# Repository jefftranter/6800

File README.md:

# 6800
Code related to the Motorola 6800 microprocessor.

Files written by me are released under the following license:

Copyright (C) by Jeff Tranter <tranter@pobox.com>

Licensed under the Apache License, Version 2.0 (the "License");
you may not use this file except in compliance with the License.
You may obtain a copy of the License at

  http://www.apache.org/licenses/LICENSE-2.0

Unless required by applicable law or agreed to in writing, software
distributed under the License is distributed on an "AS IS" BASIS,
WITHOUT WARRANTIES OR CONDITIONS OF ANY KIND, either express or implied.
See the License for the specific language governing permissions and
limitations under the License.

Documentation written by me is licensed under a Creative Commons
Attribution 4.0 International License.
See https://creativecommons.org/licenses/by/4.0/

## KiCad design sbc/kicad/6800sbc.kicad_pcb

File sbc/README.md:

6800 Single Board Computer

This is a 6800-based single board computer design. It has the
following features:

* 6802 CPU running at 1.0 MHz
* 32K of RAM
* 16K of EPROM
* Hex keypad and 7-segment LED display interface
* Parallel interface using 6821 PIA (2 8-bit parallel ports)
* Serial interface using 6850 UART with TTL levels for FTDI USB serial adaptor
* Various power options: regulated 5VDC in (e.g. via USB), unregulated 8-25 VDC in, unregulated 8-25 AC in, or 120/220 VAC in via external AC adaptor or transformer (i.e. wall-wart)
* Address decoding using CPLD (Can adjust memory map by reprogramming CPLD)
* 50/60 Hz interrupt support if powered by AC input
* Expansion connector with all CPU bus signals
* Open Source hardware design, including PCB layout, using Kicad

The design is roughly based on the Heathkit ET-6800 CPU trainer with
additional features, some taken from the Heathkit ETA-3400 expander.
It can run a modified version of the ET-6800/ET-3400 firmware and
other firmware including a serial monitor and BASIC.

MEMORY MAP

```
+----------+-----------+----------+
| Function | Addresses | Comments |
+----------+-----------+----------+
| ROM      | C000-FFFF |   16K    |
+----------+-----------+----------+
| 6850 ACIA| 8300-8301 |          |
+----------+-----------+----------+
| 6821 PIA | 8200-8203 |          |
+----------+-----------+----------+
| Display  | 8110-816F |          |
+----------+-----------+----------+
| Keyboard | 8003-800E |          |
+----------+-----------+----------+
| RAM      | 0000-7FFF |   32K    |
+----------+-----------+----------+
```

JUMPERS AND CONNECTORS

```
J1 AC/DC IN Connector to power board from unregulated AC or DC input.
J2 5V IN Connector to power board from regulated 5 Volt input.
J3 EXPANSION Connector for expansion connector to CPU bus signals.
J4 LTC Jumper to select if AC input generates IRQ or NMI interrupts.
J5 PARALLEL PORT Connector for 2 8-bit parallel i/o ports from PIA.
J6 TX DATA SELECT Jumper to select whether to use ACIA or PIA for serial output.
J7 RX DATA SELECT Jumper to select whether to use ACIA or PIA for serial input.
J8 USB POWER Jumper to select powering board from USB FTDI connector.
J9 FTDI SERIAL Connector to a 6 pin FTDI USB serial adaptor for console.
J11 SEGMENT TEST Jumper to light all LED segments for testing.
J12 REG. POWER Jumper to select powering board from unregulated AC/DC input.
J10 PA1 Jumper to select baud rate for PIA serial interface.
J13 PA2 Jumper to select baud rate for PIA serial interface.
J14 PA3 Jumper to select baud rate for PIA serial interface.
J15 PA4 Jumper to select baud rate for PIA serial interface.
J16 PA5 Jumper to select baud rate for PIA serial interface.
J17 PA6 Jumper to select baud rate for PIA serial interface.

Serial Select Jumpers:
ACIA: J6 1-2, J7 2-3
PIA:  J6 2-3, J7 1-2

Baud Rate Jumpers:
+---+---+---+---+---+---+----+
|PA1|PA2|PA3|PA4|PA5|PA6|RATE|
+---+---+---+---+---+---+----+
| H | H | H | - | - | - | 110|
| L | L | L | - | - | - | 300|
| H | L | H | - | - | - | 600|
| L | L | H | - | - | - |1200|
| H | H | L | - | - | - |2400|
| L | H | L | - | - | - |4800|
| H | L | L | - | - | - |9600|
+---+---+---+---+---+---+----+
```

ASSEMBLY NOTES

Assembly using a PCB with the provided Gerber files is straightforward
and uses all though-hole components. It is recommended to start with
lowest height components (e.g. resistors). All ICs should be mounted
on sockets. A machined socket is recommended for the EPROM so it can
be more easily replaced when reprogrammed.

You will need a way to program the EPROM and CPLD chips.

If problems are encountered, these are the most common issues to check
for:

- Check for solder opens or shorts
- Check for bent pins under IC sockets
- Check that all parts are correct values and installed with correct orientation
- Make sure PROM and CPLD are correctly programmed
- Check for 5V power, CPU clock
- Check for ACIA clock

To test memory, you can run the memory test at address EA34. It should
display the top memory address (7FFF) and increment the test cycle
count without stopping.

To test the serial output from the PIA, set jumpers for PIA output and
desired baud rate, and run the routine at EAF6. It should continuously
output "THIS IS A TERMINAL TEST".

POWER REQUIREMENTS

Typical current requirement if powered by USB is 560 mA. A 1 amp USB
power source is recommended (note that some USB power supplies and
older USB ports can only supply 0.5A).

It can be powered from unregulated AC or DC input. It can operate from
8 to 25 volts DC either polarity. Make sure the maximum voltage
rating of C2 is not exceeded. For AC input, change the value of C2 to
2000 uF or more. AC input is required if you want to use the AC line
(50/60 Hz) interrupt feature.

Current consumption for unregulated input should be between 400 and
600mA. If the 7805 regulator gets hot you might want to mount a
heatsink on it.

OTHER NOTES

If you want to use port A of the PIA for i/o, be sure to remove any
jumpers at J6, J7, and J10-J17.

The Heathkit ETA-3400 had support for a cassette tape interface. This
is not present, so any monitor or Basic commands related to cassette
will not function.

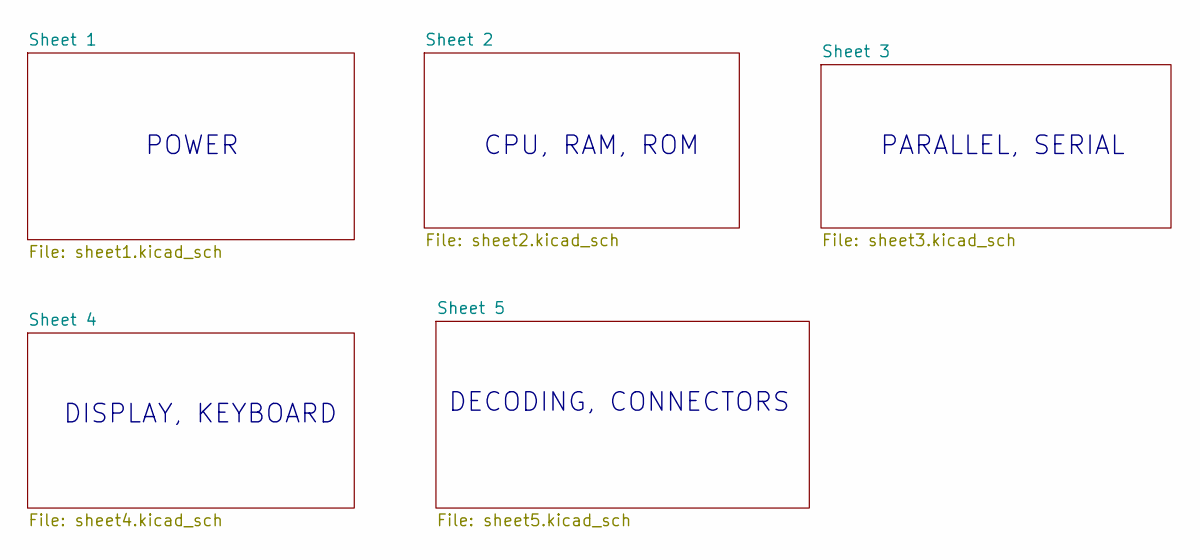
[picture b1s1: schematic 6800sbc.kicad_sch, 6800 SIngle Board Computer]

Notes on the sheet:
DECODING, CONNECTORS
PARALLEL, SERIAL
CPU, RAM, ROM
DISPLAY, KEYBOARD
POWER

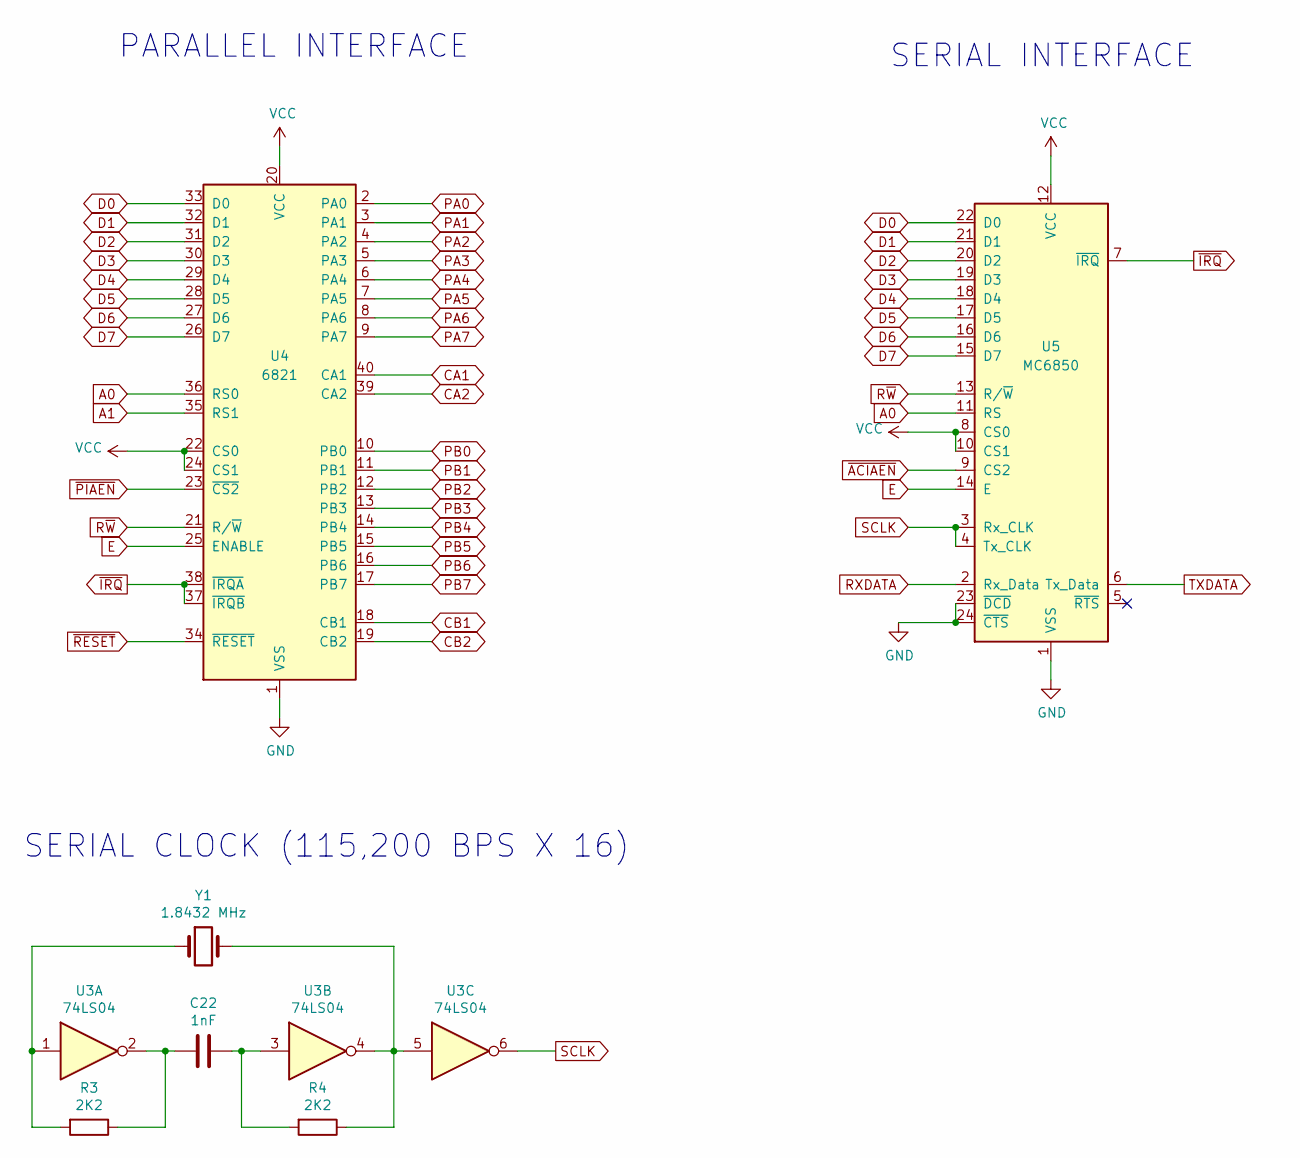
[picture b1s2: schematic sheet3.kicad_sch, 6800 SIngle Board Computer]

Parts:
C22: 1nF; C_Disc_D5.0mm_W2.5mm_P5.00mm
R3, R4: 2K2; R_Axial_DIN0204_L3.6mm_D1.6mm_P7.62mm_Horizontal
U3: 74LS04; DIP-14_W7.62mm_Socket
U4: 6821; DIP-40_W15.24mm
U5: MC6850; DIP-24_W15.24mm
Y1: 1.8432 MHz; Crystal_HC18-U_Vertical

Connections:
A0: U4.36 (RS0), U5.11 (RS); also elsewhere on the board
A1: U4.35 (RS1); also elsewhere on the board
CA1: U4.40 (CA1); also elsewhere on the board
CA2: U4.39 (CA2); also elsewhere on the board
CB1: U4.18 (CB1); also elsewhere on the board
CB2: U4.19 (CB2); also elsewhere on the board
D0: U4.33 (D0), U5.22 (D0); also elsewhere on the board
D1: U4.32 (D1), U5.21 (D1); also elsewhere on the board
D2: U4.31 (D2), U5.20 (D2); also elsewhere on the board
D3: U4.30 (D3), U5.19 (D3); also elsewhere on the board
D4: U4.29 (D4), U5.18 (D4); also elsewhere on the board
D5: U4.28 (D5), U5.17 (D5); also elsewhere on the board
D6: U4.27 (D6), U5.16 (D6); also elsewhere on the board
D7: U4.26 (D7), U5.15 (D7); also elsewhere on the board
GND: U4.1 (VSS), U5.1 (VSS), U5.23 (~DCD), U5.24 (~CTS); also elsewhere on the board
unnamed: C22.1, R4.2, U3.3
unnamed: R4.1, U3.4, U3.5, Y1.2
unnamed 154: U3.10; also elsewhere on the board
PA0: U4.2 (PA0); also elsewhere on the board
PA1: U4.3 (PA1); also elsewhere on the board
PA2: U4.4 (PA2); also elsewhere on the board
PA3: U4.5 (PA3); also elsewhere on the board
PA4: U4.6 (PA4); also elsewhere on the board
PA5: U4.7 (PA5); also elsewhere on the board
PA6: U4.8 (PA6); also elsewhere on the board
PA7: U4.9 (PA7); also elsewhere on the board
PB0: U4.10 (PB0); also elsewhere on the board
PB1: U4.11 (PB1); also elsewhere on the board
PB2: U4.12 (PB2); also elsewhere on the board
PB3: U4.13 (PB3); also elsewhere on the board
PB4: U4.14 (PB4); also elsewhere on the board
PB5: U4.15 (PB5); also elsewhere on the board
PB6: U4.16 (PB6); also elsewhere on the board
PB7: U4.17 (PB7); also elsewhere on the board
RXDATA: U5.2 (Rx_Data); also elsewhere on the board
SCLK: U3.6, U5.3 (Rx_CLK), U5.4 (Tx_CLK); also elsewhere on the board
TXDATA: U5.6 (Tx_Data); also elsewhere on the board
VCC: U4.20 (VCC), U4.22 (CS0), U4.24 (CS1), U5.8 (CS0), U5.10 (CS1), U5.12 (VCC); also elsewhere on the board
~ACIAEN: U5.9 (CS2); also elsewhere on the board
~IRQ: U4.37 (~IRQB), U4.38 (~IRQA), U5.7 (~IRQ); also elsewhere on the board
~PIAEN: U4.23 (~CS2); also elsewhere on the board
~RESET: U4.34 (~RESET); also elsewhere on the board

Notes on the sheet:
PARALLEL INTERFACE
SERIAL CLOCK (115,200 BPS X 16)
SERIAL INTERFACE

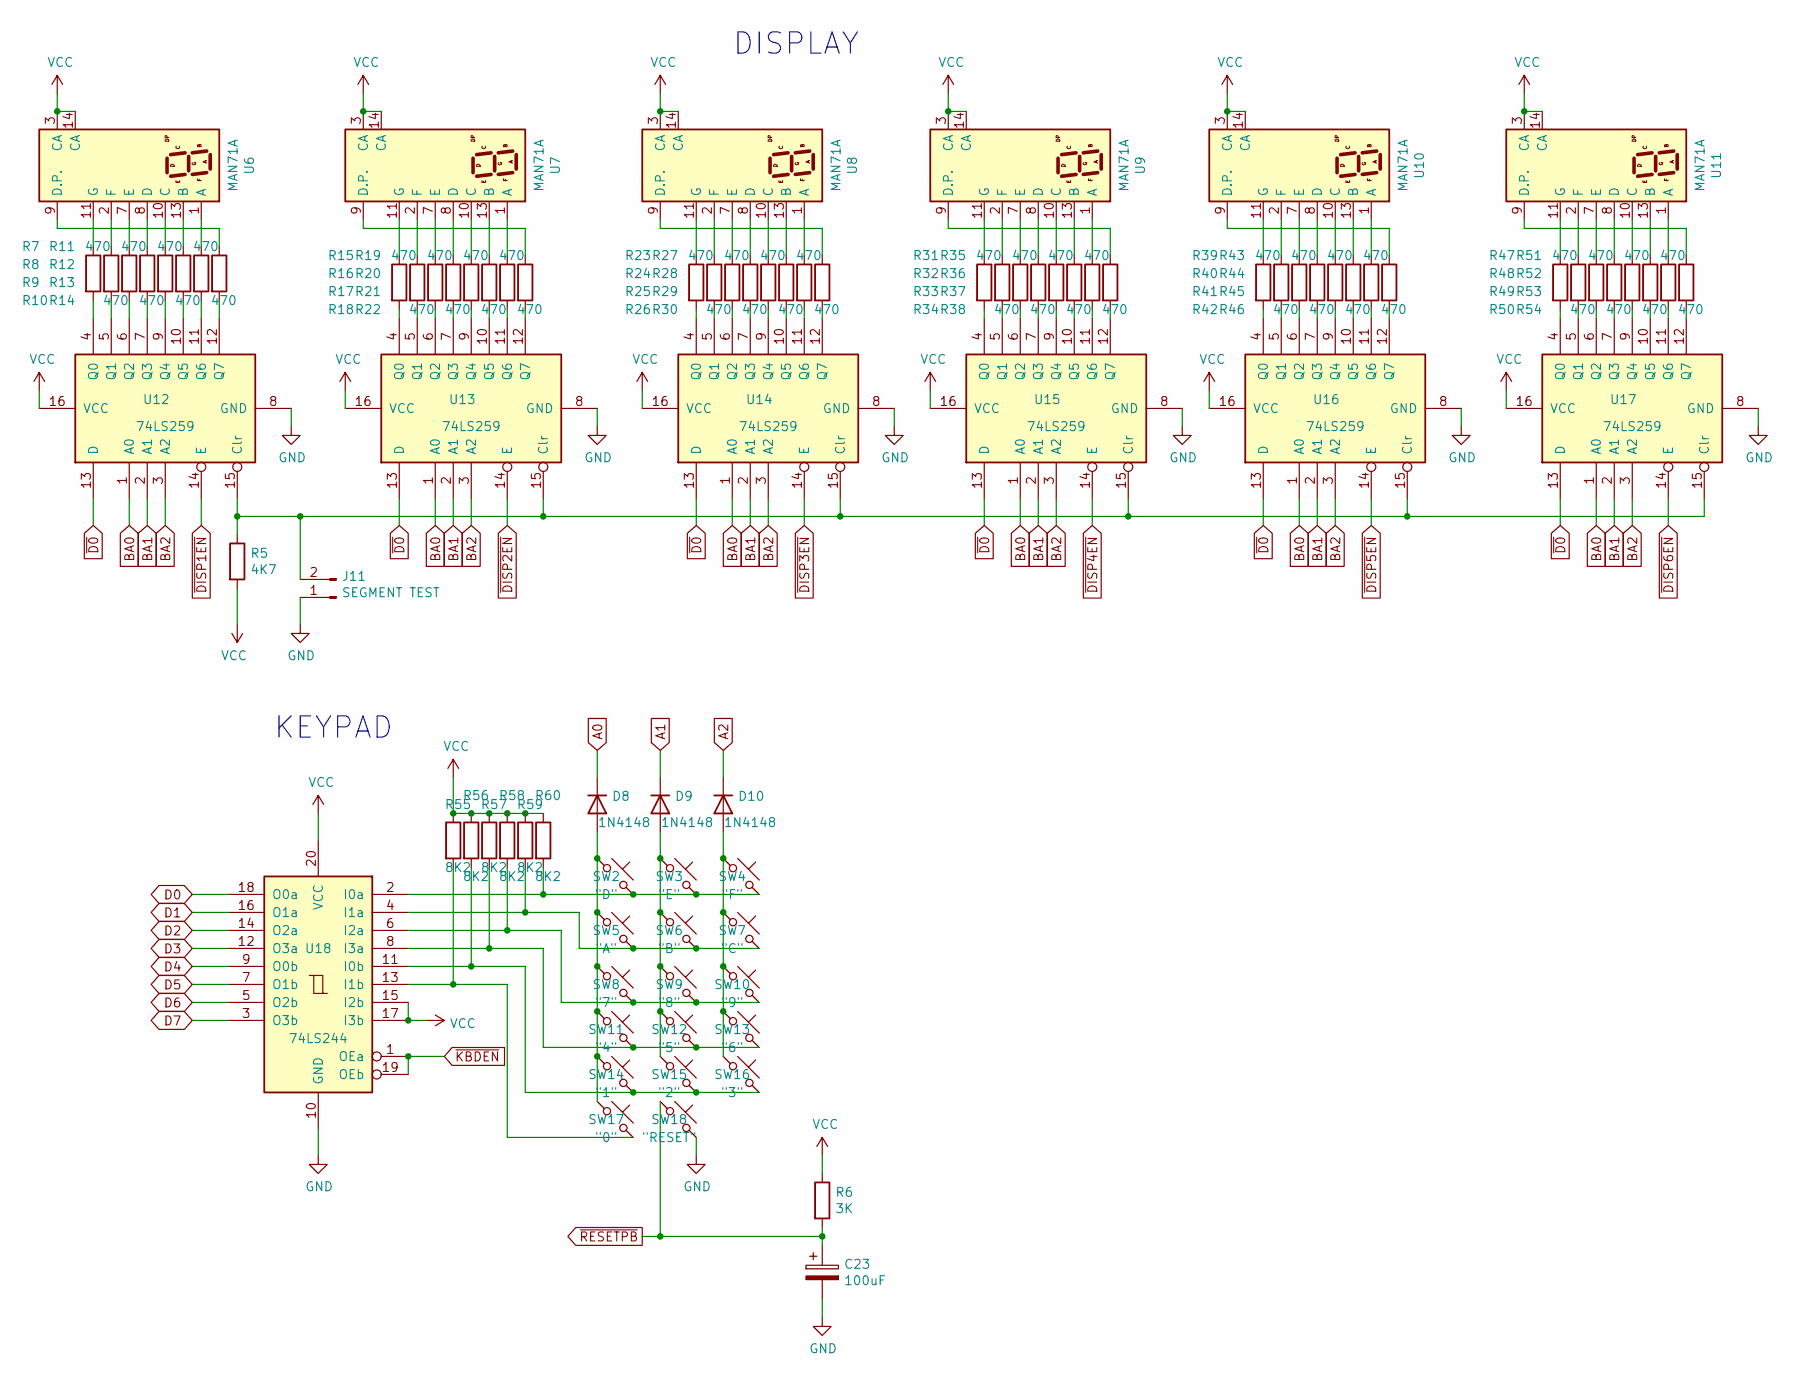
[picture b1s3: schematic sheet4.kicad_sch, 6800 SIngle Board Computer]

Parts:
C23: 100uF; CP_Radial_D4.0mm_P2.00mm
D8, D9, D10: 1N4148; D_DO-35_SOD27_P7.62mm_Horizontal
J11: SEGMENT TEST; PinHeader_1x02_P2.54mm_Vertical
R5: 4K7; R_Axial_DIN0204_L3.6mm_D1.6mm_P7.62mm_Horizontal
R6: 3K; R_Axial_DIN0204_L3.6mm_D1.6mm_P7.62mm_Horizontal
R7, R8, R9, R10, R11, R12, R13, R14, R15, R16, R17, R18, R19, R20, R21, R22, R23, R24, R25, R26, R27, R28, R29, R30, R31, R32, R33, R34, R35, R36, R37, R38, R39, R40, R41, R42, R43, R44, R45, R46, R47, R48, R49, R50, R51, R52, R53, R54: 470; R_Axial_DIN0204_L3.6mm_D1.6mm_P7.62mm_Horizontal
R55, R56, R57, R58, R59, R60: 8K2; R_Axial_DIN0204_L3.6mm_D1.6mm_P7.62mm_Horizontal
SW2: "D"; SW_PUSH_6mm_H4.3mm
SW3: "E"; SW_PUSH_6mm_H4.3mm
SW4: "F"; SW_PUSH_6mm_H4.3mm
SW5: "A"; SW_PUSH_6mm_H4.3mm
SW6: "B"; SW_PUSH_6mm_H4.3mm
SW7: "C"; SW_PUSH_6mm_H4.3mm
SW8: "7"; SW_PUSH_6mm_H4.3mm
SW9: "8"; SW_PUSH_6mm_H4.3mm
SW10: "9"; SW_PUSH_6mm_H4.3mm
SW11: "4"; SW_PUSH_6mm_H4.3mm
SW12: "5"; SW_PUSH_6mm_H4.3mm
SW13: "6"; SW_PUSH_6mm_H4.3mm
SW14: "1"; SW_PUSH_6mm_H4.3mm
SW15: "2"; SW_PUSH_6mm_H4.3mm
SW16: "3"; SW_PUSH_6mm_H4.3mm
SW17: "0"; SW_PUSH_6mm_H4.3mm
SW18: "RESET"; SW_PUSH_6mm_H4.3mm
U6, U7, U8, U9, U10, U11: MAN71A
U12, U13, U14, U15, U16, U17: 74LS259; DIP-16_W7.62mm_Socket
U18: 74LS244; DIP-20_W7.62mm_Socket

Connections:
A0: D8.1 (K); also elsewhere on the board
A1: D9.1 (K); also elsewhere on the board
A2: D10.1 (K); also elsewhere on the board
BA0: U12.1 (A0), U13.1 (A0), U14.1 (A0), U15.1 (A0), U16.1 (A0), U17.1 (A0); also elsewhere on the board
BA1: U12.2 (A1), U13.2 (A1), U14.2 (A1), U15.2 (A1), U16.2 (A1), U17.2 (A1); also elsewhere on the board
BA2: U12.3 (A2), U13.3 (A2), U14.3 (A2), U15.3 (A2), U16.3 (A2), U17.3 (A2); also elsewhere on the board
D0: U18.18 (O0a); also elsewhere on the board
D1: U18.16 (O1a); also elsewhere on the board
D2: U18.14 (O2a); also elsewhere on the board
D3: U18.12 (O3a); also elsewhere on the board
D4: U18.9 (O0b); also elsewhere on the board
D5: U18.7 (O1b); also elsewhere on the board
D6: U18.5 (O2b); also elsewhere on the board
D7: U18.3 (O3b); also elsewhere on the board
GND: C23.2, J11.1, SW18.2, U12.8 (GND), U13.8 (GND), U14.8 (GND), U15.8 (GND), U16.8 (GND), U17.8 (GND), U18.10 (GND); also elsewhere on the board
unnamed: D8.2 (A), SW2.1, SW5.1, SW8.1, SW11.1, SW14.1, SW17.1
unnamed: D9.2 (A), SW3.1, SW6.1, SW9.1, SW12.1, SW15.1
unnamed: D10.2 (A), SW4.1, SW7.1, SW10.1, SW13.1, SW16.1
unnamed: J11.2, R5.1, U12.15 (Clr), U13.15 (Clr), U14.15 (Clr), U15.15 (Clr), U16.15 (Clr), U17.15 (Clr)
unnamed: R7.1, U6.11 (G)
unnamed: R7.2, U12.4 (Q0)
unnamed: R8.1, U6.2 (F)
unnamed: R8.2, U12.5 (Q1)
unnamed: R9.1, U6.7 (E)
unnamed: R9.2, U12.6 (Q2)
unnamed: R10.1, U6.8 (D)
unnamed: R10.2, U12.7 (Q3)
unnamed: R11.1, U6.10 (C)
unnamed: R11.2, U12.9 (Q4)
unnamed: R12.1, U6.13 (B)
unnamed: R12.2, U12.10 (Q5)
unnamed: R13.1, U6.1 (A)
unnamed: R13.2, U12.11 (Q6)
unnamed: R14.1, U6.9 (D.P.)
unnamed: R14.2, U12.12 (Q7)
unnamed: R15.1, U7.11 (G)
unnamed: R15.2, U13.4 (Q0)
unnamed: R16.1, U7.2 (F)
unnamed: R16.2, U13.5 (Q1)
unnamed: R17.1, U7.7 (E)
unnamed: R17.2, U13.6 (Q2)
unnamed: R18.1, U7.8 (D)
unnamed: R18.2, U13.7 (Q3)
unnamed: R19.1, U7.10 (C)
unnamed: R19.2, U13.9 (Q4)
unnamed: R20.1, U7.13 (B)
unnamed: R20.2, U13.10 (Q5)
unnamed: R21.1, U7.1 (A)
unnamed: R21.2, U13.11 (Q6)
unnamed: R22.1, U7.9 (D.P.)
unnamed: R22.2, U13.12 (Q7)
unnamed: R23.1, U8.11 (G)
unnamed: R23.2, U14.4 (Q0)
unnamed: R24.1, U8.2 (F)
unnamed: R24.2, U14.5 (Q1)
unnamed: R25.1, U8.7 (E)
unnamed: R25.2, U14.6 (Q2)
unnamed: R26.1, U8.8 (D)
unnamed: R26.2, U14.7 (Q3)
unnamed: R27.1, U8.10 (C)
unnamed: R27.2, U14.9 (Q4)
unnamed: R28.1, U8.13 (B)
unnamed: R28.2, U14.10 (Q5)
unnamed: R29.1, U8.1 (A)
unnamed: R29.2, U14.11 (Q6)
unnamed: R30.1, U8.9 (D.P.)
unnamed: R30.2, U14.12 (Q7)
unnamed: R31.1, U9.11 (G)
unnamed: R31.2, U15.4 (Q0)
unnamed: R32.1, U9.2 (F)
unnamed: R32.2, U15.5 (Q1)
unnamed: R33.1, U9.7 (E)
unnamed: R33.2, U15.6 (Q2)
unnamed: R34.1, U9.8 (D)
unnamed: R34.2, U15.7 (Q3)
unnamed: R35.1, U9.10 (C)
unnamed: R35.2, U15.9 (Q4)
unnamed: R36.1, U9.13 (B)
unnamed: R36.2, U15.10 (Q5)
unnamed: R37.1, U9.1 (A)
unnamed: R37.2, U15.11 (Q6)
unnamed: R38.1, U9.9 (D.P.)
unnamed: R38.2, U15.12 (Q7)
unnamed: R39.1, U10.11 (G)
unnamed: R39.2, U16.4 (Q0)
unnamed: R40.1, U10.2 (F)
unnamed: R40.2, U16.5 (Q1)
unnamed: R41.1, U10.7 (E)
unnamed: R41.2, U16.6 (Q2)
unnamed: R42.1, U10.8 (D)
unnamed: R42.2, U16.7 (Q3)
unnamed: R43.1, U10.10 (C)
unnamed: R43.2, U16.9 (Q4)
unnamed: R44.1, U10.13 (B)
unnamed: R44.2, U16.10 (Q5)
unnamed: R45.1, U10.1 (A)
unnamed: R45.2, U16.11 (Q6)
unnamed: R46.1, U10.9 (D.P.)
unnamed: R46.2, U16.12 (Q7)
unnamed: R47.1, U11.11 (G)
unnamed: R47.2, U17.4 (Q0)
unnamed: R48.1, U11.2 (F)
unnamed: R48.2, U17.5 (Q1)
unnamed: R49.1, U11.7 (E)
unnamed: R49.2, U17.6 (Q2)
unnamed: R50.1, U11.8 (D)
unnamed: R50.2, U17.7 (Q3)
unnamed: R51.1, U11.10 (C)
unnamed: R51.2, U17.9 (Q4)
unnamed: R52.1, U11.13 (B)
unnamed: R52.2, U17.10 (Q5)
unnamed: R53.1, U11.1 (A)
unnamed: R53.2, U17.11 (Q6)
unnamed: R54.1, U11.9 (D.P.)
unnamed: R54.2, U17.12 (Q7)
unnamed: R55.2, SW17.2, U18.13 (I1b)
unnamed: R56.2, SW14.2, SW15.2, SW16.2, U18.11 (I0b)
unnamed: R57.2, SW11.2, SW12.2, SW13.2, U18.8 (I3a)
unnamed: R58.2, SW8.2, SW9.2, SW10.2, U18.6 (I2a)
unnamed: R59.2, SW5.2, SW6.2, SW7.2, U18.4 (I1a)
unnamed: R60.2, SW2.2, SW3.2, SW4.2, U18.2 (I0a)
VCC: R5.2, R6.1, R55.1, R56.1, R57.1, R58.1, R59.1, R60.1, U6.3 (CA), U6.14 (CA), U7.3 (CA), U7.14 (CA), U8.3 (CA), U8.14 (CA), U9.3 (CA), U9.14 (CA), U10.3 (CA), U10.14 (CA), U11.3 (CA), U11.14 (CA), U12.16 (VCC), U13.16 (VCC), U14.16 (VCC), U15.16 (VCC), U16.16 (VCC), U17.16 (VCC), U18.15 (I2b), U18.17 (I3b), U18.20 (VCC); also elsewhere on the board
~D0: U12.13 (D), U13.13 (D), U14.13 (D), U15.13 (D), U16.13 (D), U17.13 (D); also elsewhere on the board
~DISP1EN: U12.14 (E); also elsewhere on the board
~DISP2EN: U13.14 (E); also elsewhere on the board
~DISP3EN: U14.14 (E); also elsewhere on the board
~DISP4EN: U15.14 (E); also elsewhere on the board
~DISP5EN: U16.14 (E); also elsewhere on the board
~DISP6EN: U17.14 (E); also elsewhere on the board
~KBDEN: U18.1 (OEa), U18.19 (OEb); also elsewhere on the board
~RESETPB: C23.1, R6.2, SW18.1; also elsewhere on the board

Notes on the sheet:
DISPLAY
KEYPAD

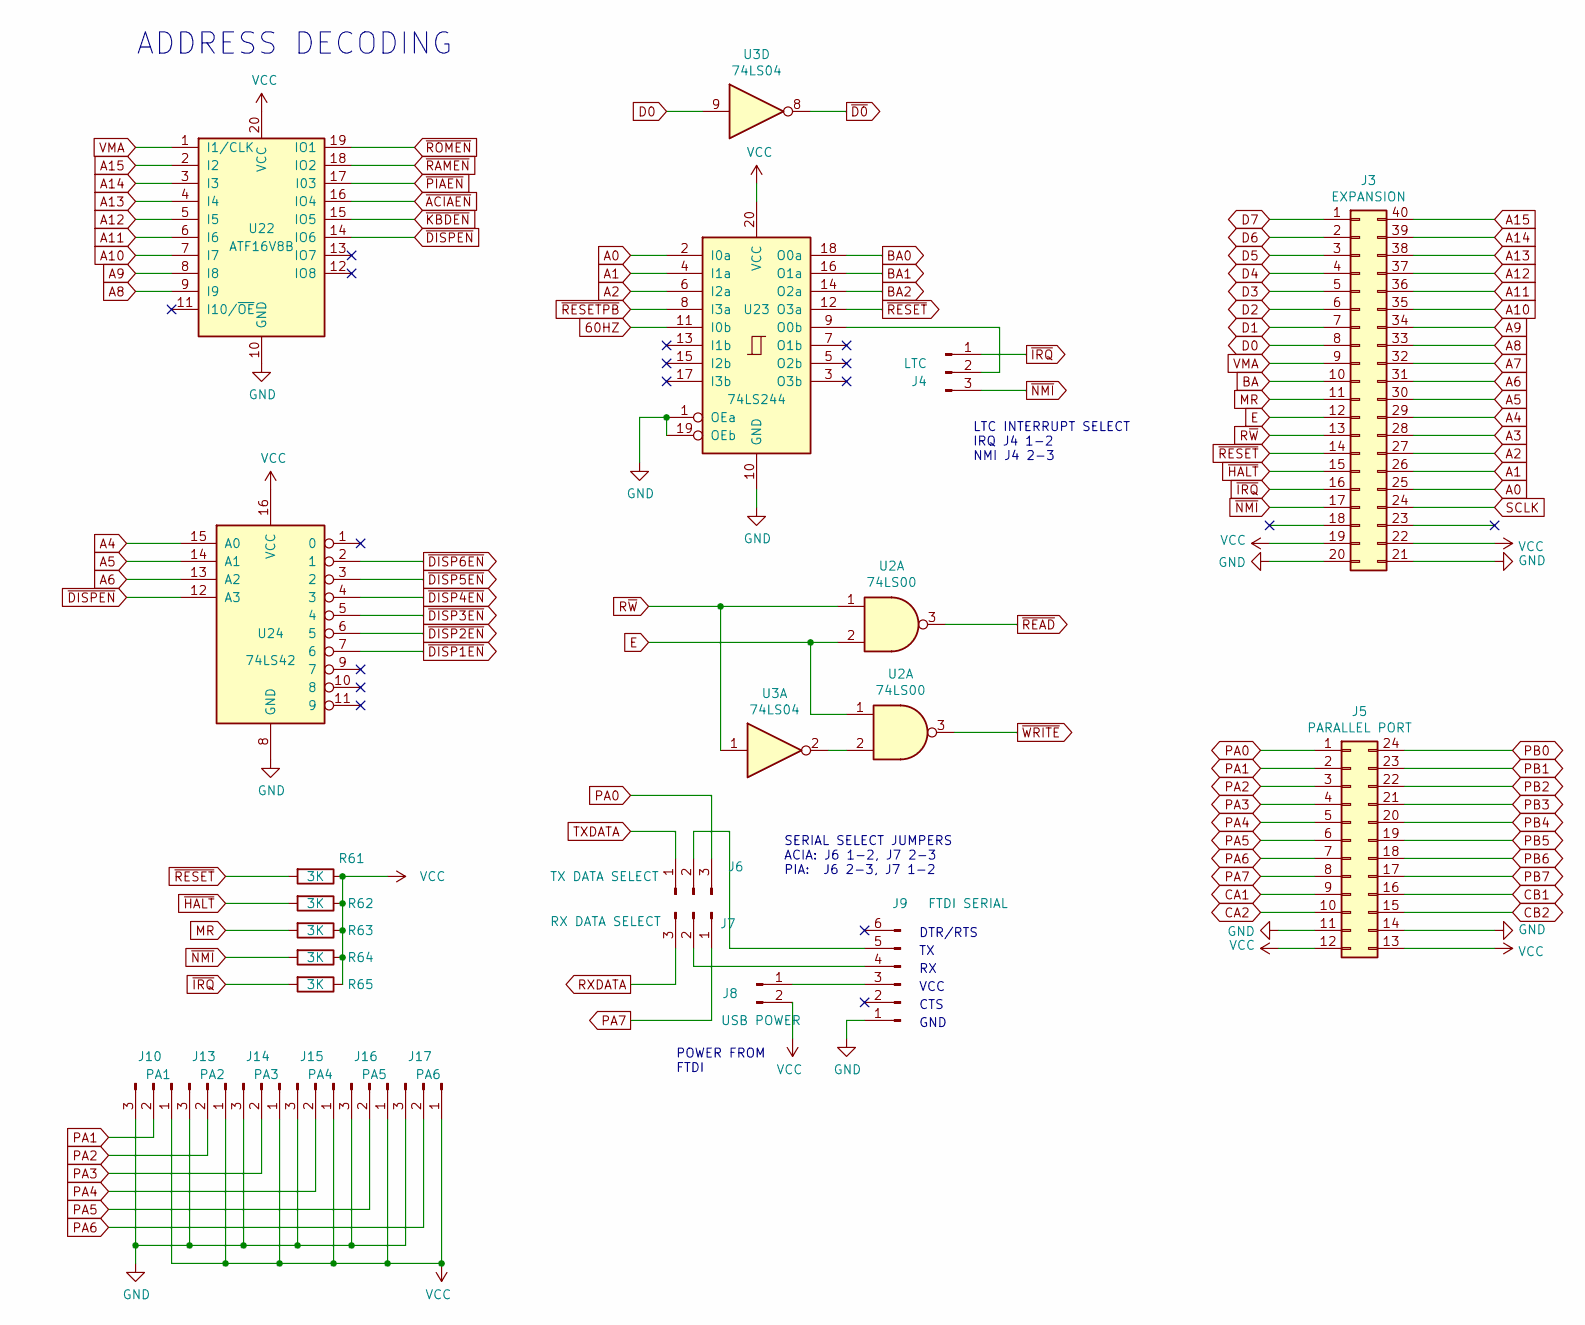
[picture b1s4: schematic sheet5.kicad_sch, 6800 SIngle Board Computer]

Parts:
J3: EXPANSION; PinHeader_2x20_P2.54mm_Vertical
J4: LTC; PinHeader_1x03_P2.54mm_Vertical
J5: PARALLEL PORT; PinHeader_2x12_P2.54mm_Vertical
J6: TX DATA SELECT; PinHeader_1x03_P2.54mm_Vertical
J7: RX DATA SELECT; PinHeader_1x03_P2.54mm_Vertical
J8: USB POWER; PinHeader_1x02_P2.54mm_Vertical
J9: FTDI SERIAL; PinHeader_1x06_P2.54mm_Vertical
J10: PA1; PinHeader_1x03_P2.54mm_Vertical
J13: PA2; PinHeader_1x03_P2.54mm_Vertical
J14: PA3; PinHeader_1x03_P2.54mm_Vertical
J15: PA4; PinHeader_1x03_P2.54mm_Vertical
J16: PA5; PinHeader_1x03_P2.54mm_Vertical
J17: PA6; PinHeader_1x03_P2.54mm_Vertical
R61, R62, R63, R64, R65: 3K; R_Axial_DIN0204_L3.6mm_D1.6mm_P7.62mm_Horizontal
U2: 74LS00; DIP-14_W7.62mm_Socket
U3: 74LS04; DIP-14_W7.62mm_Socket
U22: ATF16V8B; DIP-20_W7.62mm_Socket
U23: 74LS244; DIP-20_W7.62mm_Socket
U24: 74LS42; DIP-16_W7.62mm_Socket

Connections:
60HZ: U23.11 (I0b); also elsewhere on the board
A0: J3.25, U23.2 (I0a); also elsewhere on the board
A1: J3.26, U23.4 (I1a); also elsewhere on the board
A2: J3.27, U23.6 (I2a); also elsewhere on the board
A3: J3.28; also elsewhere on the board
A4: J3.29, U24.15 (A0); also elsewhere on the board
A5: J3.30, U24.14 (A1); also elsewhere on the board
A6: J3.31, U24.13 (A2); also elsewhere on the board
A7: J3.32; also elsewhere on the board
A8: J3.33, U22.9 (I9); also elsewhere on the board
A9: J3.34, U22.8 (I8); also elsewhere on the board
A10: J3.35, U22.7 (I7); also elsewhere on the board
A11: J3.36, U22.6 (I6); also elsewhere on the board
A12: J3.37, U22.5 (I5); also elsewhere on the board
A13: J3.38, U22.4 (I4); also elsewhere on the board
A14: J3.39, U22.3 (I3); also elsewhere on the board
A15: J3.40, U22.2 (I2); also elsewhere on the board
BA: J3.10; also elsewhere on the board
BA0: U23.18 (O0a); also elsewhere on the board
BA1: U23.16 (O1a); also elsewhere on the board
BA2: U23.14 (O2a); also elsewhere on the board
CA1: J5.9; also elsewhere on the board
CA2: J5.10; also elsewhere on the board
CB1: J5.16; also elsewhere on the board
CB2: J5.15; also elsewhere on the board
D0: J3.8, U3.9; also elsewhere on the board
D1: J3.7; also elsewhere on the board
D2: J3.6; also elsewhere on the board
D3: J3.5; also elsewhere on the board
D4: J3.4; also elsewhere on the board
D5: J3.3; also elsewhere on the board
D6: J3.2; also elsewhere on the board
D7: J3.1; also elsewhere on the board
GND: J3.20, J3.21, J5.11, J5.14, J9.1, J10.3, J13.3, J14.3, J15.3, J16.3, J17.3, U22.10 (GND), U23.1 (OEa), U23.10 (GND), U23.19 (OEb), U24.8 (GND); also elsewhere on the board
MR: J3.11, R63.2; also elsewhere on the board
unnamed: J4.2, U23.9 (O0b)
unnamed: J6.2, J9.5
unnamed: J7.2, J9.4
unnamed: J8.1, J9.3
unnamed: U2.5, U3.10
PA0: J5.1, J6.3; also elsewhere on the board
PA1: J5.2, J10.2; also elsewhere on the board
PA2: J5.3, J13.2; also elsewhere on the board
PA3: J5.4, J14.2; also elsewhere on the board
PA4: J5.5, J15.2; also elsewhere on the board
PA5: J5.6, J16.2; also elsewhere on the board
PA6: J5.7, J17.2; also elsewhere on the board
PA7: J5.8, J7.1; also elsewhere on the board
PB0: J5.24; also elsewhere on the board
PB1: J5.23; also elsewhere on the board
PB2: J5.22; also elsewhere on the board
PB3: J5.21; also elsewhere on the board
PB4: J5.20; also elsewhere on the board
PB5: J5.19; also elsewhere on the board
PB6: J5.18; also elsewhere on the board
PB7: J5.17; also elsewhere on the board
RXDATA: J7.3; also elsewhere on the board
SCLK: J3.24; also elsewhere on the board
TXDATA: J6.1; also elsewhere on the board
VCC: J3.19, J3.22, J5.12, J5.13, J8.2, J10.1, J13.1, J14.1, J15.1, J16.1, J17.1, R61.1, R62.1, R63.1, R64.1, R65.1, U22.20 (VCC), U23.20 (VCC), U24.16 (VCC); also elsewhere on the board
VMA: J3.9, U22.1 (I1/CLK); also elsewhere on the board
~ACIAEN: U22.16 (IO4); also elsewhere on the board
~D0: U3.8; also elsewhere on the board
~DISP1EN: U24.7 (6); also elsewhere on the board
~DISP2EN: U24.6 (5); also elsewhere on the board
~DISP3EN: U24.5 (4); also elsewhere on the board
~DISP4EN: U24.4 (3); also elsewhere on the board
~DISP5EN: U24.3 (2); also elsewhere on the board
~DISP6EN: U24.2 (1); also elsewhere on the board
~DISPEN: U22.14 (IO6), U24.12 (A3)
~HALT: J3.15, R62.2; also elsewhere on the board
~IRQ: J3.16, J4.1, R65.2; also elsewhere on the board
~KBDEN: U22.15 (IO5); also elsewhere on the board
~NMI: J3.17, J4.3, R64.2; also elsewhere on the board
~PIAEN: U22.17 (I03); also elsewhere on the board
~RAMEN: U22.18 (IO2); also elsewhere on the board
~RESET: J3.14, R61.2, U23.12 (O3a); also elsewhere on the board
~RESETPB: U23.8 (I3a); also elsewhere on the board
~ROMEN: U22.19 (IO1); also elsewhere on the board
~WRITE: U2.6; also elsewhere on the board

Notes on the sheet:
SERIAL SELECT JUMPERS ACIA: J6 1-2, J7 2-3 PIA: J6 2-3, J7 1-2
CTS
VCC
LTC INTERRUPT SELECT IRQ J4 1-2 NMI J4 2-3
POWER FROM FTDI
ADDRESS DECODING
DTR/RTS
GND

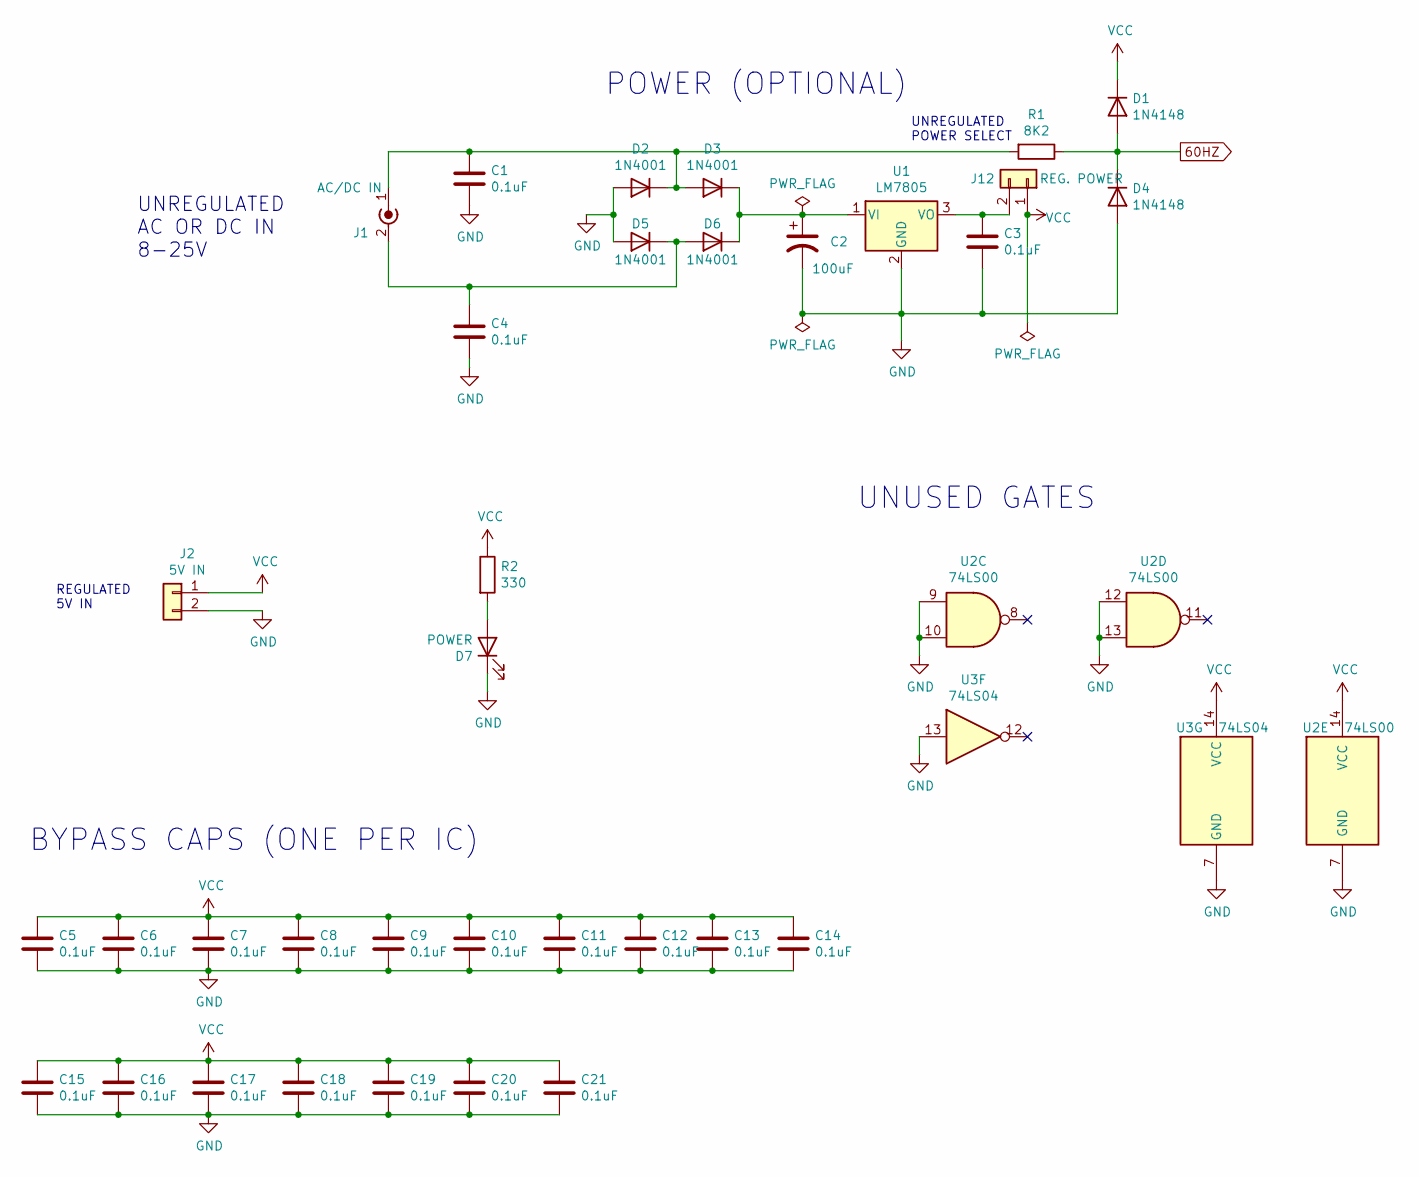
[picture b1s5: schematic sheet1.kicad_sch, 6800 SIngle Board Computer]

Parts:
C1, C3, C4, C5, C6, C7, C8, C9, C10, C11, C12, C13, C14, C15, C16, C17, C18, C19, C20, C21: 0.1uF; C_Disc_D4.3mm_W1.9mm_P5.00mm
C2: 100uF; CP_Radial_D5.0mm_P2.00mm
D1, D4: 1N4148; D_DO-35_SOD27_P7.62mm_Horizontal
D2, D3, D5, D6: 1N4001; D_DO-41_SOD81_P10.16mm_Horizontal
D7: POWER; LED_D2.0mm_W4.8mm_H2.5mm_FlatTop
J1: AC/DC IN; PinHeader_1x02_P2.54mm_Vertical
J2: 5V IN; PinHeader_1x02_P2.54mm_Vertical
J12: REG. POWER; PinHeader_1x02_P2.54mm_Vertical
R1: 8K2; R_Axial_DIN0204_L3.6mm_D1.6mm_P7.62mm_Horizontal
R2: 330; R_Axial_DIN0204_L3.6mm_D1.6mm_P7.62mm_Horizontal
U1: LM7805; TO-220-3_Vertical
U2: 74LS00; DIP-14_W7.62mm_Socket
U3: 74LS04; DIP-14_W7.62mm_Socket

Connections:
60HZ: D1.2 (A), D4.1 (K), R1.1; also elsewhere on the board
GND: C1.2, C2.2, C3.2, C4.2, C5.2, C6.2, C7.2, C8.2, C9.2, C10.2, C11.2, C12.2, C13.2, C14.2, C15.2, C16.2, C17.2, C18.2, C19.2, C20.2, C21.2, D2.2 (A), D4.2 (A), D5.2 (A), D7.1 (K), J2.2, U1.2 (GND), U2.7 (GND), U2.9, U2.10, U2.12, U2.13, U3.7 (GND), U3.13; also elsewhere on the board
unnamed: C1.1, D2.1 (K), D3.2 (A), J1.1 (In), R1.2
unnamed: C2.1, D3.1 (K), D6.1 (K), U1.1 (VI)
unnamed: C3.1, J12.2, U1.3 (VO)
unnamed: C4.1, D5.1 (K), D6.2 (A), J1.2 (Ext)
unnamed: D7.2 (A), R2.2
unnamed: U2.5, U3.10
VCC: C5.1, C6.1, C7.1, C8.1, C9.1, C10.1, C11.1, C12.1, C13.1, C14.1, C15.1, C16.1, C17.1, C18.1, C19.1, C20.1, C21.1, D1.1 (K), J2.1, J12.1, R2.1, U2.14 (VCC), U3.14 (VCC); also elsewhere on the board
~WRITE: U2.6; also elsewhere on the board

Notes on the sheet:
BYPASS CAPS (ONE PER IC)
UNREGULATED POWER SELECT
UNREGULATED AC OR DC IN 8-25V
UNUSED GATES
REGULATED 5V IN
POWER (OPTIONAL)

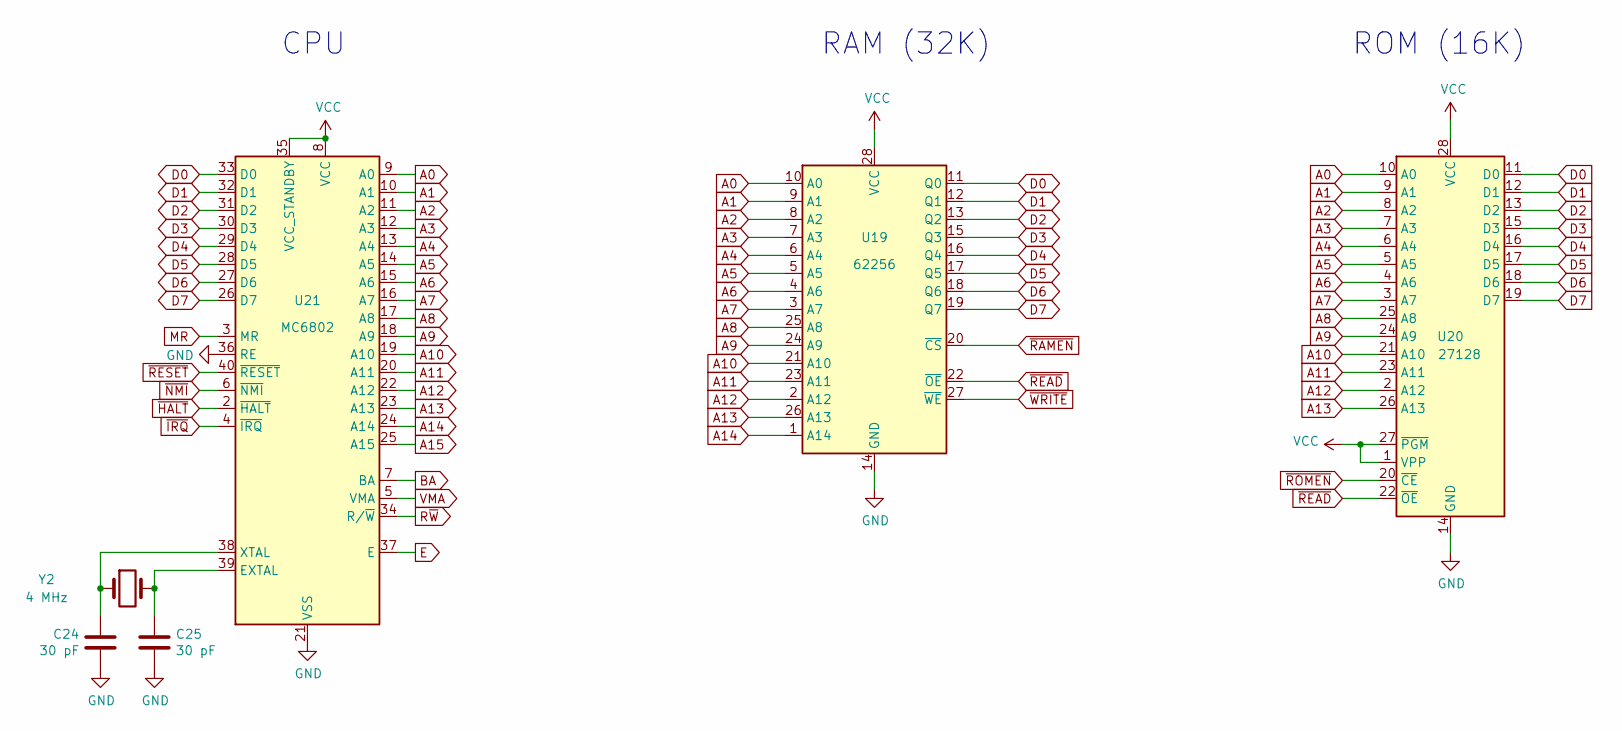
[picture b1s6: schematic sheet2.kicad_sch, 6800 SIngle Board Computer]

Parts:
C24, C25: 30 pF; C_Disc_D5.0mm_W2.5mm_P5.00mm
U19: 62256; DIP-28_W15.24mm
U20: 27128; DIP-28_W15.24mm
U21: MC6802; DIP-40_W15.24mm
Y2: 4 MHz; Crystal_HC18-U_Vertical

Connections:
A0: U19.10 (A0), U20.10 (A0), U21.9 (A0); also elsewhere on the board
A1: U19.9 (A1), U20.9 (A1), U21.10 (A1); also elsewhere on the board
A2: U19.8 (A2), U20.8 (A2), U21.11 (A2); also elsewhere on the board
A3: U19.7 (A3), U20.7 (A3), U21.12 (A3); also elsewhere on the board
A4: U19.6 (A4), U20.6 (A4), U21.13 (A4); also elsewhere on the board
A5: U19.5 (A5), U20.5 (A5), U21.14 (A5); also elsewhere on the board
A6: U19.4 (A6), U20.4 (A6), U21.15 (A6); also elsewhere on the board
A7: U19.3 (A7), U20.3 (A7), U21.16 (A7); also elsewhere on the board
A8: U19.25 (A8), U20.25 (A8), U21.17 (A8); also elsewhere on the board
A9: U19.24 (A9), U20.24 (A9), U21.18 (A9); also elsewhere on the board
A10: U19.21 (A10), U20.21 (A10), U21.19 (A10); also elsewhere on the board
A11: U19.23 (A11), U20.23 (A11), U21.20 (A11); also elsewhere on the board
A12: U19.2 (A12), U20.2 (A12), U21.22 (A12); also elsewhere on the board
A13: U19.26 (A13), U20.26 (A13), U21.23 (A13); also elsewhere on the board
A14: U19.1 (A14), U21.24 (A14); also elsewhere on the board
A15: U21.25 (A15); also elsewhere on the board
BA: U21.7 (BA); also elsewhere on the board
D0: U19.11 (Q0), U20.11 (D0), U21.33 (D0); also elsewhere on the board
D1: U19.12 (Q1), U20.12 (D1), U21.32 (D1); also elsewhere on the board
D2: U19.13 (Q2), U20.13 (D2), U21.31 (D2); also elsewhere on the board
D3: U19.15 (Q3), U20.15 (D3), U21.30 (D3); also elsewhere on the board
D4: U19.16 (Q4), U20.16 (D4), U21.29 (D4); also elsewhere on the board
D5: U19.17 (Q5), U20.17 (D5), U21.28 (D5); also elsewhere on the board
D6: U19.18 (Q6), U20.18 (D6), U21.27 (D6); also elsewhere on the board
D7: U19.19 (Q7), U20.19 (D7), U21.26 (D7); also elsewhere on the board
GND: C24.1, C25.2, U19.14 (GND), U20.14 (GND), U21.1 (VSS), U21.21 (VSS), U21.36 (RE); also elsewhere on the board
MR: U21.3 (MR); also elsewhere on the board
unnamed: C24.2, U21.38 (XTAL), Y2.1
unnamed: C25.1, U21.39 (EXTAL), Y2.2
VCC: U19.28 (VCC), U20.1 (VPP), U20.27 (~PGM), U20.28 (VCC), U21.8 (VCC), U21.35 (VCC_STANDBY); also elsewhere on the board
VMA: U21.5 (VMA); also elsewhere on the board
~HALT: U21.2 (~HALT); also elsewhere on the board
~IRQ: U21.4 (~IRQ); also elsewhere on the board
~NMI: U21.6 (~NMI); also elsewhere on the board
~RAMEN: U19.20 (~CS); also elsewhere on the board
~RESET: U21.40 (~RESET); also elsewhere on the board
~ROMEN: U20.20 (~CE); also elsewhere on the board
~WRITE: U19.27 (~WE); also elsewhere on the board

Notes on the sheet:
ROM (16K)
CPU
RAM (32K)

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

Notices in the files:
sbc/kicad/6800sbc.kicad_pcb:
(c) 2022 Jeff Tranter
